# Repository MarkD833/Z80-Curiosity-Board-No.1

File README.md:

# Zilog Z80 Curiosity Board #1

I've recently had time to go back to my youth and re-discover some of the microprocessors that were available at the time. This is my first Z80 board. I wanted to put together a small board that had a Z80 as well as PIO (parallel I/O), SIO (serial I/O) and CTC (Counter Timer) chips.

I chose to use PLCC devices to try and keep the board size small enough to keep the costs down at JLCPCB. That decision proved to be a problem as I thought I'd sourced some SIO/2 chips in PLCC44 packaging. Unfortunately my source let me down and I decided to go with an SC16C2554 DUART instead.

## Description

The aim of this project is to see if I can build my own Z80 based system to experiment on. As well as the Z80 processor (Z84C0020VEC), it will have some parallel I/O (Z84C2010VEG), serial I/O (SC16C2554) and some counter timers (Z84C3010VEC) . I also wanted to see if I could port CP/M to this hardware as an additional challenge, so the design would need a CompactFlash card interface. My starting point for CP/M was Grant Searles excellent [web page](http://searle.x10host.com/cpm/index.html).

## Design

The design is fairly straightforward, using a skinny 64Kb SRAM from my stash as well as a 64Kb EEPROM for non volatile storage.

I studied other designs that I came across and liked a concept that I came across whereby on startup, the whole of the ROM was copied into RAM and then the ROM disabled. The hardware was configured so that the ROM and the RAM both occupied the same 64Kb, but initially any read accessed would go to the ROM and any write accesses would go to the RAM. Once the ROM was copied into RAM (at the same addresses), the ROM would be disabled giving full read/write access to the RAM and the Z80 would continue to execute instructions as if nothing had happened.

The design uses simple logic chips to handle the address decoding, as well as the disabling of the ROM etc.

# The board layout

This is an annotated 3D view of the board generated by Kicad as it stands at v1.1.

# Software

I adapted Dave Dunfields MONZ80 monitor program to work with this board. MONZ80 can be found on [Dave's website](https://dunfield.themindfactory.com/dnldsrc.htm) as part of the MONITORS.ZIP file. There is no documentation for the monitor but most of the commands are self explanatory.

The monitor code needs tweeking to support the specific UART hardware I am using but that simply involves providing code to initialise the UART and code to output a characher/byte as well as read in a character/byte. My modified version of MONZ80 is in the code folder and has been edited to allow assembly using the free online assembler at [ASM80.COM](https://asm80.com) - select the Z80 CPU.

# Known errors

* The initial design messed up the addressing of the DUART chip such that only one serial port was available. Cutting a few tracks and adding a few jumper wires sorted that error out. The changes are detailed on the Kicad schematic.

* The choice of the SC16C2554 DUART meant that I couldn't use IM2 for interrupts. The initial code for the interrupt handlers had to be at the start of memory - just where CP/M also needed to store information. 

# Conclusions

The board works, but sadly not how I had hoped due to the interrupt issue mentioned above.

It is possible to run CP/M on this board once the files are loaded onto the CompactFlash card. That is where the issue lies. It is possible to follow Grant Searles instructions on transferring files onto the CF card using the DOWNLOAD command and the packaging tool, but in order to do so, there needs to be pauses between lines and between characters when sending the files over as there is no way for the CP/M system to use an interrupt driven serial handler to buffer the data.

## License

This project is licensed under the GNU General Public License v3.0 - see the LICENSE.md file for details

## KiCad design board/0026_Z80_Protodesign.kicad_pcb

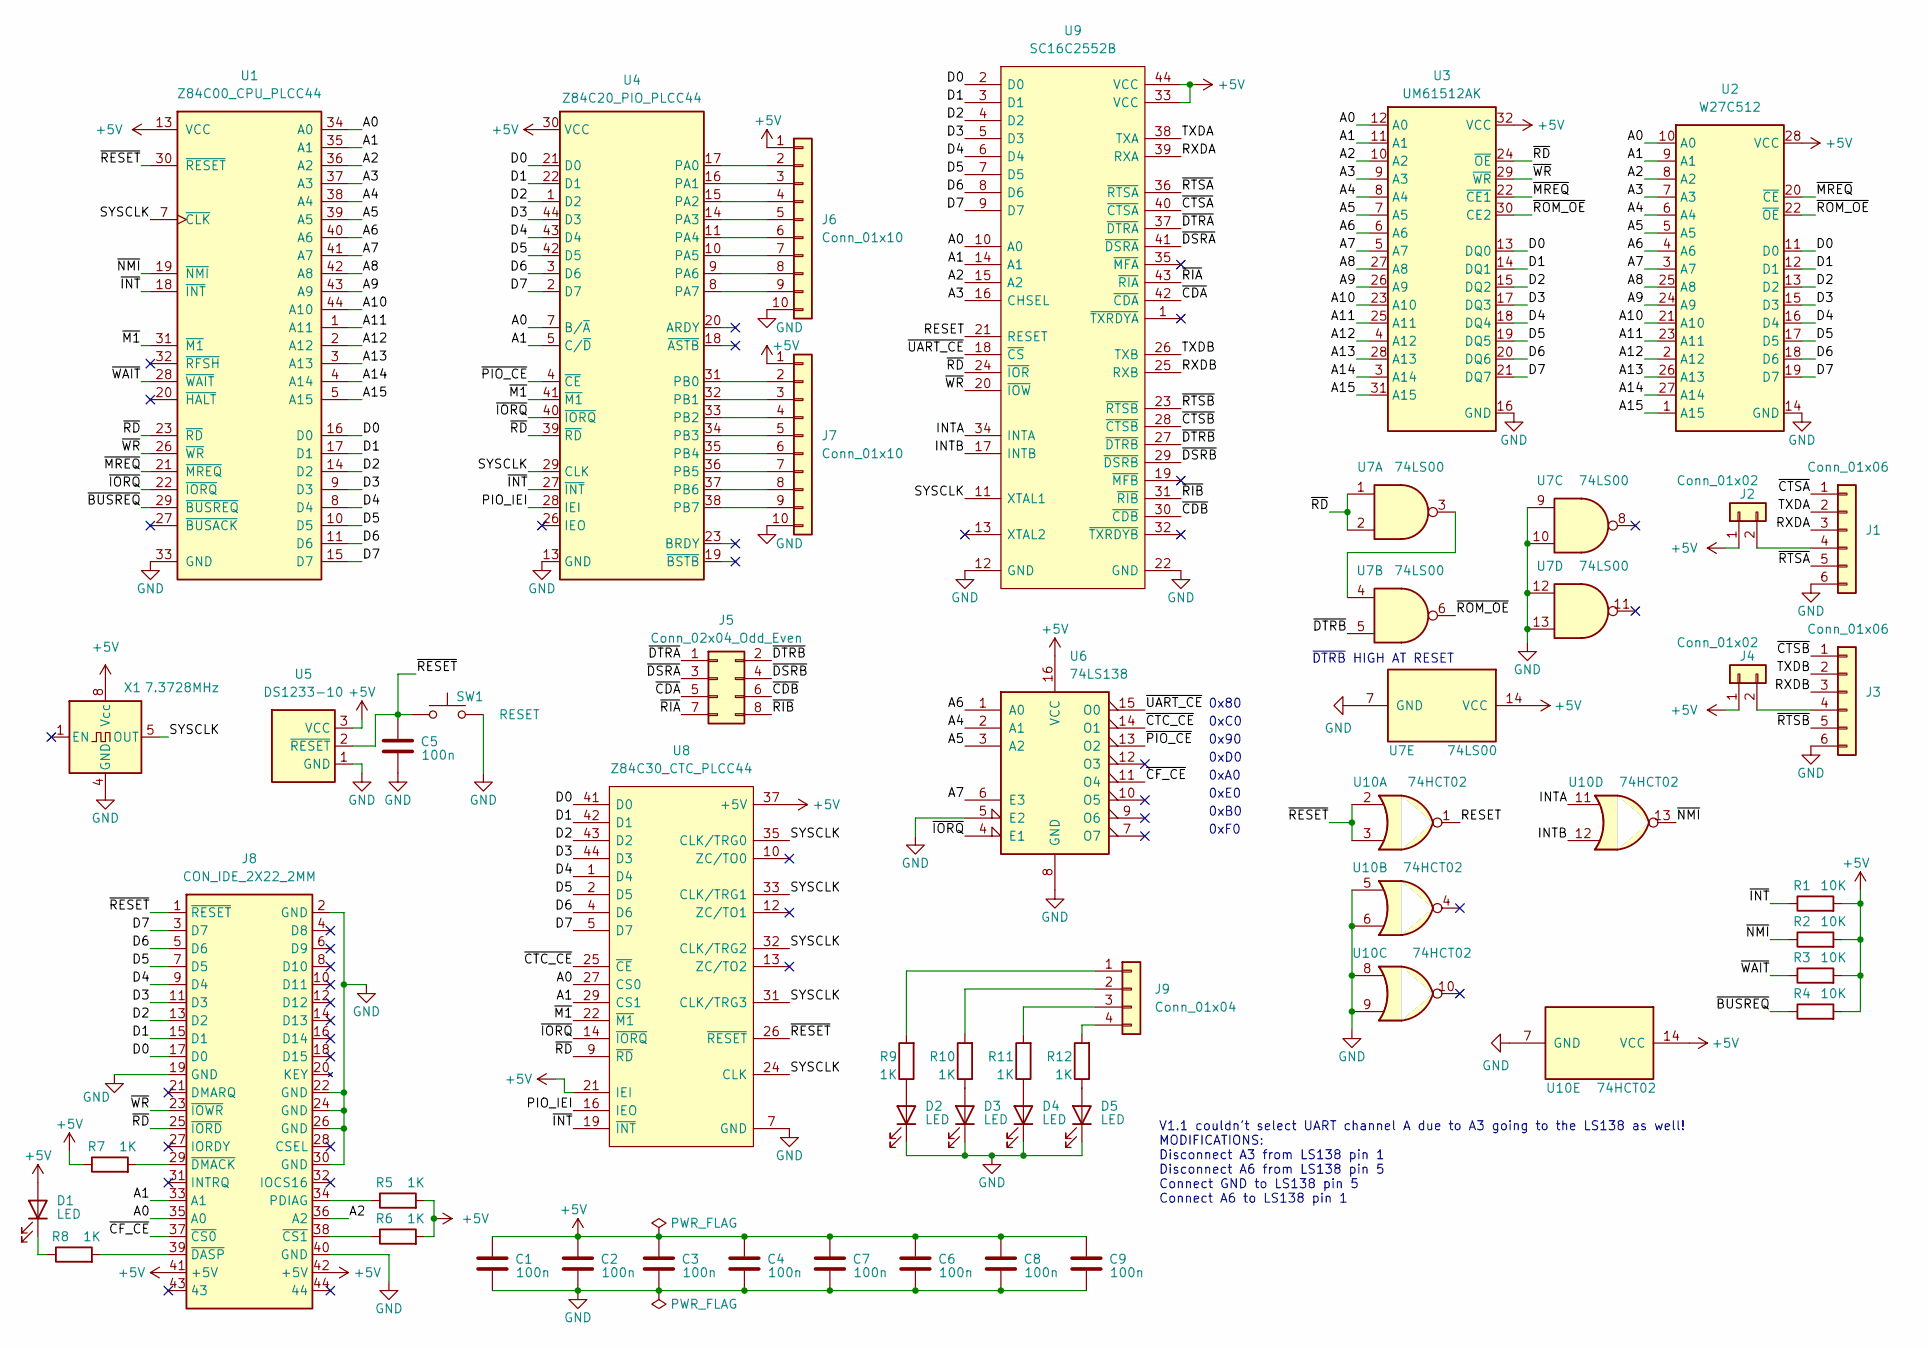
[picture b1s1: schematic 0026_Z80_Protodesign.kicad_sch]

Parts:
C1, C2, C3, C4, C5, C6, C7, C8, C9: 100n; C_0805_2012Metric_Pad1.18x1.45mm_HandSolder
D1, D2, D3, D4, D5: LED; LED_0805_2012Metric_Pad1.15x1.40mm_HandSolder
J1, J3: Conn_01x06; PinHeader_1x06_P2.54mm_Vertical
J2, J4: Conn_01x02; PinHeader_1x02_P2.54mm_Vertical
J5: Conn_02x04_Odd_Even; PinHeader_2x04_P2.54mm_Vertical
J6, J7: Conn_01x10; PinHeader_1x10_P2.54mm_Vertical
J8: CON_IDE_2X22_2MM; CompactFlashHeader_2x22_P2.00mm_Vertical
J9: Conn_01x04; PinHeader_1x04_P2.54mm_Vertical
R1, R2, R3, R4: 10K; R_0805_2012Metric_Pad1.20x1.40mm_HandSolder
R5, R6, R7, R8, R9, R10, R11, R12: 1K; R_0805_2012Metric_Pad1.20x1.40mm_HandSolder
SW1: RESET; TACTILE_SWITCH_SMD_6.0X3.5MM
U1: Z84C00_CPU_PLCC44; PLCC-44_THT-Socket
U2: W27C512; DIP-28_W15.24mm
U3: UM61512AK; DIP-32_W7.62mm
U4: Z84C20_PIO_PLCC44; PLCC-44_THT-Socket
U5: DS1233-10; TO-92L_Inline
U6: 74LS138; DIP-16_W7.62mm_Socket
U7: 74LS00; DIP-14_W7.62mm_Socket
U8: Z84C30_CTC_PLCC44; PLCC-44_THT-Socket; Manufacturer_Part_Number Z84C3010PEG
U9: SC16C2552B; PLCC-44_THT-Socket
U10: 74HCT02; DIP-14_W7.62mm_Socket
X1: 7.3728MHz; Oscillator_DIP-8

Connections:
+5V: C1.2, C2.2, C3.2, C4.2, C6.2, C7.2, C8.2, C9.2, D1.2 (A), J2.1, J4.1, J6.1, J7.1, J8.41 (+5V), J8.42 (+5V), R1.2, R2.2, R3.2, R4.2, R5.2, R6.2, R7.1, U1.13 (VCC), U2.28 (VCC), U3.32 (VCC), U4.30 (VCC), U5.3 (VCC), U6.16 (VCC), U7.14 (VCC), U8.21 (IEI), U8.37 (+5V), U9.33 (VCC), U9.44 (VCC), U10.14 (VCC), X1.8 (Vcc)
/A0: J8.35 (A0), U1.34 (A0), U2.10 (A0), U3.12 (A0), U4.7 (B/~A), U8.27 (CS0), U9.10 (A0)
/A1: J8.33 (A1), U1.35 (A1), U2.9 (A1), U3.11 (A1), U4.5 (C/~D), U8.29 (CS1), U9.14 (A1)
/A2: J8.36 (A2), U1.36 (A2), U2.8 (A2), U3.10 (A2), U9.15 (A2)
/A4: U1.38 (A4), U2.6 (A4), U3.8 (A4), U6.2 (A1)
/A5: U1.39 (A5), U2.5 (A5), U3.7 (A5), U6.3 (A2)
/A7: U1.41 (A7), U2.3 (A7), U3.5 (A7), U6.6 (E3)
/A8: U1.42 (A8), U2.25 (A8), U3.27 (A8)
/A9: U1.43 (A9), U2.24 (A9), U3.26 (A9)
/A10: U1.44 (A10), U2.21 (A10), U3.23 (A10)
/A11: U1.1 (A11), U2.23 (A11), U3.25 (A11)
/A12: U1.2 (A12), U2.2 (A12), U3.4 (A12)
/A13: U1.3 (A13), U2.26 (A13), U3.28 (A13)
/A14: U1.4 (A14), U2.27 (A14), U3.3 (A14)
/A15: U1.5 (A15), U2.1 (A15), U3.31 (A15)
/D0: J8.17 (D0), U1.16 (D0), U2.11 (D0), U3.13 (DQ0), U4.21 (D0), U8.41 (D0), U9.2 (D0)
/D1: J8.15 (D1), U1.17 (D1), U2.12 (D1), U3.14 (DQ1), U4.22 (D1), U8.42 (D1), U9.3 (D1)
/D2: J8.13 (D2), U1.14 (D2), U2.13 (D2), U3.15 (DQ2), U4.1 (D2), U8.43 (D2), U9.4 (D2)
/D3: J8.11 (D3), U1.9 (D3), U2.15 (D3), U3.17 (DQ3), U4.44 (D3), U8.44 (D3), U9.5 (D3)
/D4: J8.9 (D4), U1.8 (D4), U2.16 (D4), U3.18 (DQ4), U4.43 (D4), U8.1 (D4), U9.6 (D4)
/D5: J8.7 (D5), U1.10 (D5), U2.17 (D5), U3.19 (DQ5), U4.42 (D5), U8.2 (D5), U9.7 (D5)
/D6: J8.5 (D6), U1.11 (D6), U2.18 (D6), U3.20 (DQ6), U4.3 (D6), U8.4 (D6), U9.8 (D6)
/D7: J8.3 (D7), U1.15 (D7), U2.19 (D7), U3.21 (DQ7), U4.2 (D7), U8.5 (D7), U9.9 (D7)
/INTA: U9.34 (INTA), U10.11
/INTB: U9.17 (INTB), U10.12
/PIO_IEI: U4.28 (IEI), U8.16 (IEO)
/RESET: U9.21 (RESET), U10.1
/RXDA: J1.3, U9.39 (RXA)
/RXDB: J3.3, U9.25 (RXB)
/SYSCLK: U1.7 (~CLK), U4.29 (CLK), U8.24 (CLK), U8.31 (CLK/TRG3), U8.32 (CLK/TRG2), U8.33 (CLK/TRG1), U8.35 (CLK/TRG0), U9.11 (XTAL1), X1.5 (OUT)
/TXDA: J1.2, U9.38 (TXA)
/TXDB: J3.2, U9.26 (TXB)
/~BUSREQ: R4.1, U1.29 (~BUSREQ)
/~CDA: J5.5, U9.42 (~CDA)
/~CDB: J5.6, U9.30 (~CDB)
/~CF_CE: J8.37 (~CS0), U6.11 (O4)
/~CTC_CE: U6.14 (O1), U8.25 (~CE)
/~CTSA: J1.1, U9.40 (~CTSA)
/~CTSB: J3.1, U9.28 (~CTSB)
/~DSRA: J5.3, U9.41 (~DSRA)
/~DSRB: J5.4, U9.29 (~DSRB)
/~DTRA: J5.1, U9.37 (~DTRA)
/~DTRB: J5.2, U7.5, U9.27 (~DTRB)
/~INT: R1.1, U1.18 (~INT), U4.27 (~INT), U8.19 (~INT)
/~IORQ: U1.22 (~IORQ), U4.40 (~IORQ), U6.4 (E1), U8.14 (~IORQ)
/~M1: U1.31 (~M1), U4.41 (~M1), U8.22 (~M1)
/~MREQ: U1.21 (~MREQ), U2.20 (~CE), U3.22 (~CE1)
/~NMI: R2.1, U1.19 (~NMI), U10.13
/~PIO_CE: U4.4 (~CE), U6.13 (O2)
/~RD: J8.25 (~IORD), U1.23 (~RD), U3.24 (~OE), U4.39 (~RD), U7.1, U7.2, U8.9 (~RD), U9.24 (~IOR)
/~RESET: C5.2, J8.1 (~RESET), SW1.1, U1.30 (~RESET), U5.2 (~RESET), U8.26 (~RESET), U10.2, U10.3
/~RIA: J5.7, U9.43 (~RIA)
/~RIB: J5.8, U9.31 (~RIB)
/~ROM_OE: U2.22 (~OE), U3.30 (CE2), U7.6
/~RTSA: J1.5, U9.36 (~RTSA)
/~RTSB: J3.5, U9.23 (~RTSB)
/~UART_CE: U6.15 (O0), U9.18 (~CS)
/~WAIT: R3.1, U1.28 (~WAIT)
/~WR: J8.23 (~IOWR), U1.26 (~WR), U3.29 (~WR), U9.20 (~IOW)
unnamed: D1.1 (K), R8.1
unnamed: D2.2 (A), R9.1
unnamed: D3.2 (A), R10.1
unnamed: D4.2 (A), R11.1
unnamed: D5.2 (A), R12.1
unnamed: J1.4, J2.2
unnamed: J3.4, J4.2
unnamed: J6.2, U4.17 (PA0)
unnamed: J6.3, U4.16 (PA1)
unnamed: J6.4, U4.15 (PA2)
unnamed: J6.5, U4.14 (PA3)
unnamed: J6.6, U4.11 (PA4)
unnamed: J6.7, U4.10 (PA5)
unnamed: J6.8, U4.9 (PA6)
unnamed: J6.9, U4.8 (PA7)
unnamed: J7.2, U4.31 (PB0)
unnamed: J7.3, U4.32 (PB1)
unnamed: J7.4, U4.33 (PB2)
unnamed: J7.5, U4.34 (PB3)
unnamed: J7.6, U4.35 (PB4)
unnamed: J7.7, U4.36 (PB5)
unnamed: J7.8, U4.37 (PB6)
unnamed: J7.9, U4.38 (PB7)
unnamed: J8.34 (PDIAG), R5.1
unnamed: J8.38 (~CS1), R6.1
unnamed: J8.39 (~DASP), R8.2
unnamed: J8.29 (~DMACK), R7.2
unnamed: J9.1, R9.2
unnamed: J9.2, R10.2
unnamed: J9.3, R11.2
unnamed: J9.4, R12.2
unnamed: U7.3, U7.4

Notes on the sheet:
0xC0
0x80
0xE0
0xA0
0xD0
V1.1 couldn't select UART channel A due to A3 going to the LS138 as well! MODIFICATIONS: Disconnect A3 from LS138 pin 1 Disconnect A6 from LS138 pin 5 Connect GND to LS138 pin 5 Connect A6 to LS138 pin 1
0xB0
0xF0
~{DTRB} HIGH AT RESET
0x90

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
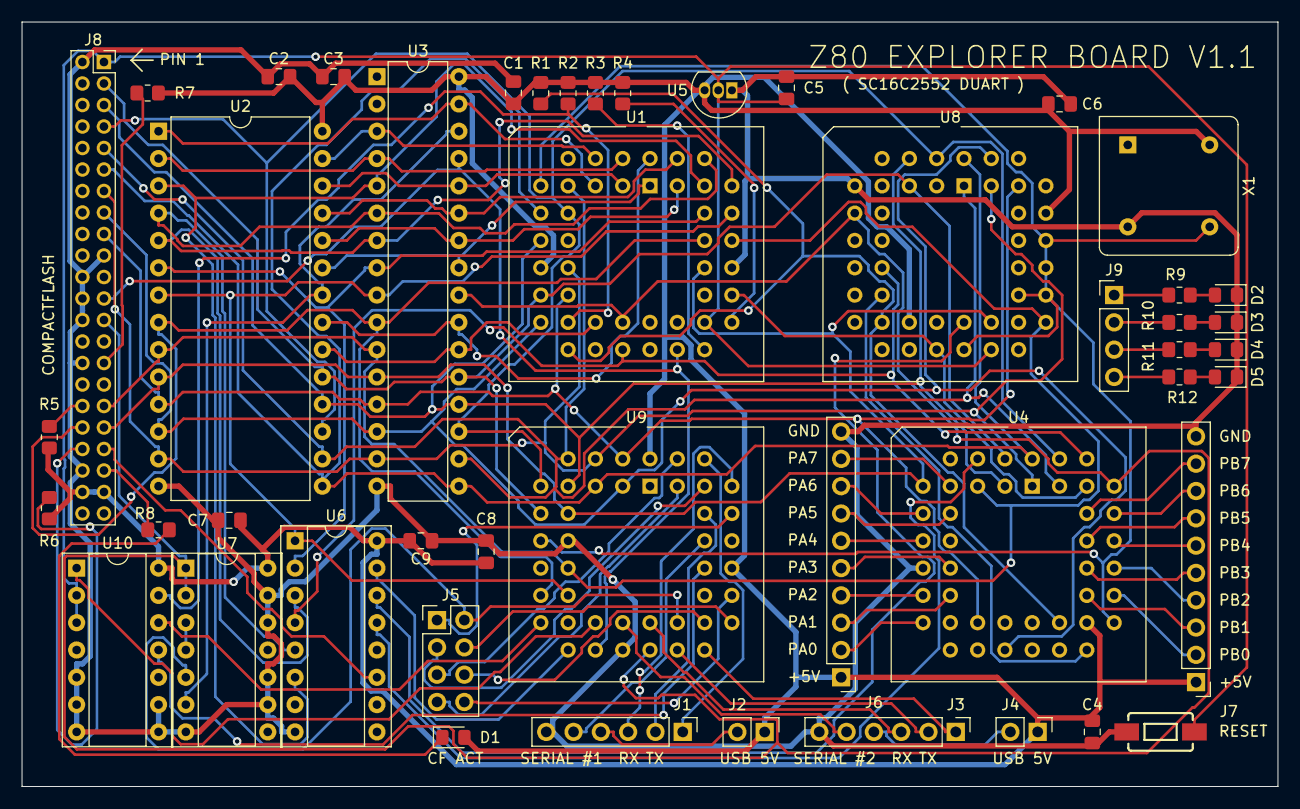
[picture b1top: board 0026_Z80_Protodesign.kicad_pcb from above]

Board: 2 copper layers, 116.8 x 71.1 mm, 47 parts (0 on the bottom side), 94 nets.

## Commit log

2024-08-18 first save
2024-08-18 removed border on layout image
